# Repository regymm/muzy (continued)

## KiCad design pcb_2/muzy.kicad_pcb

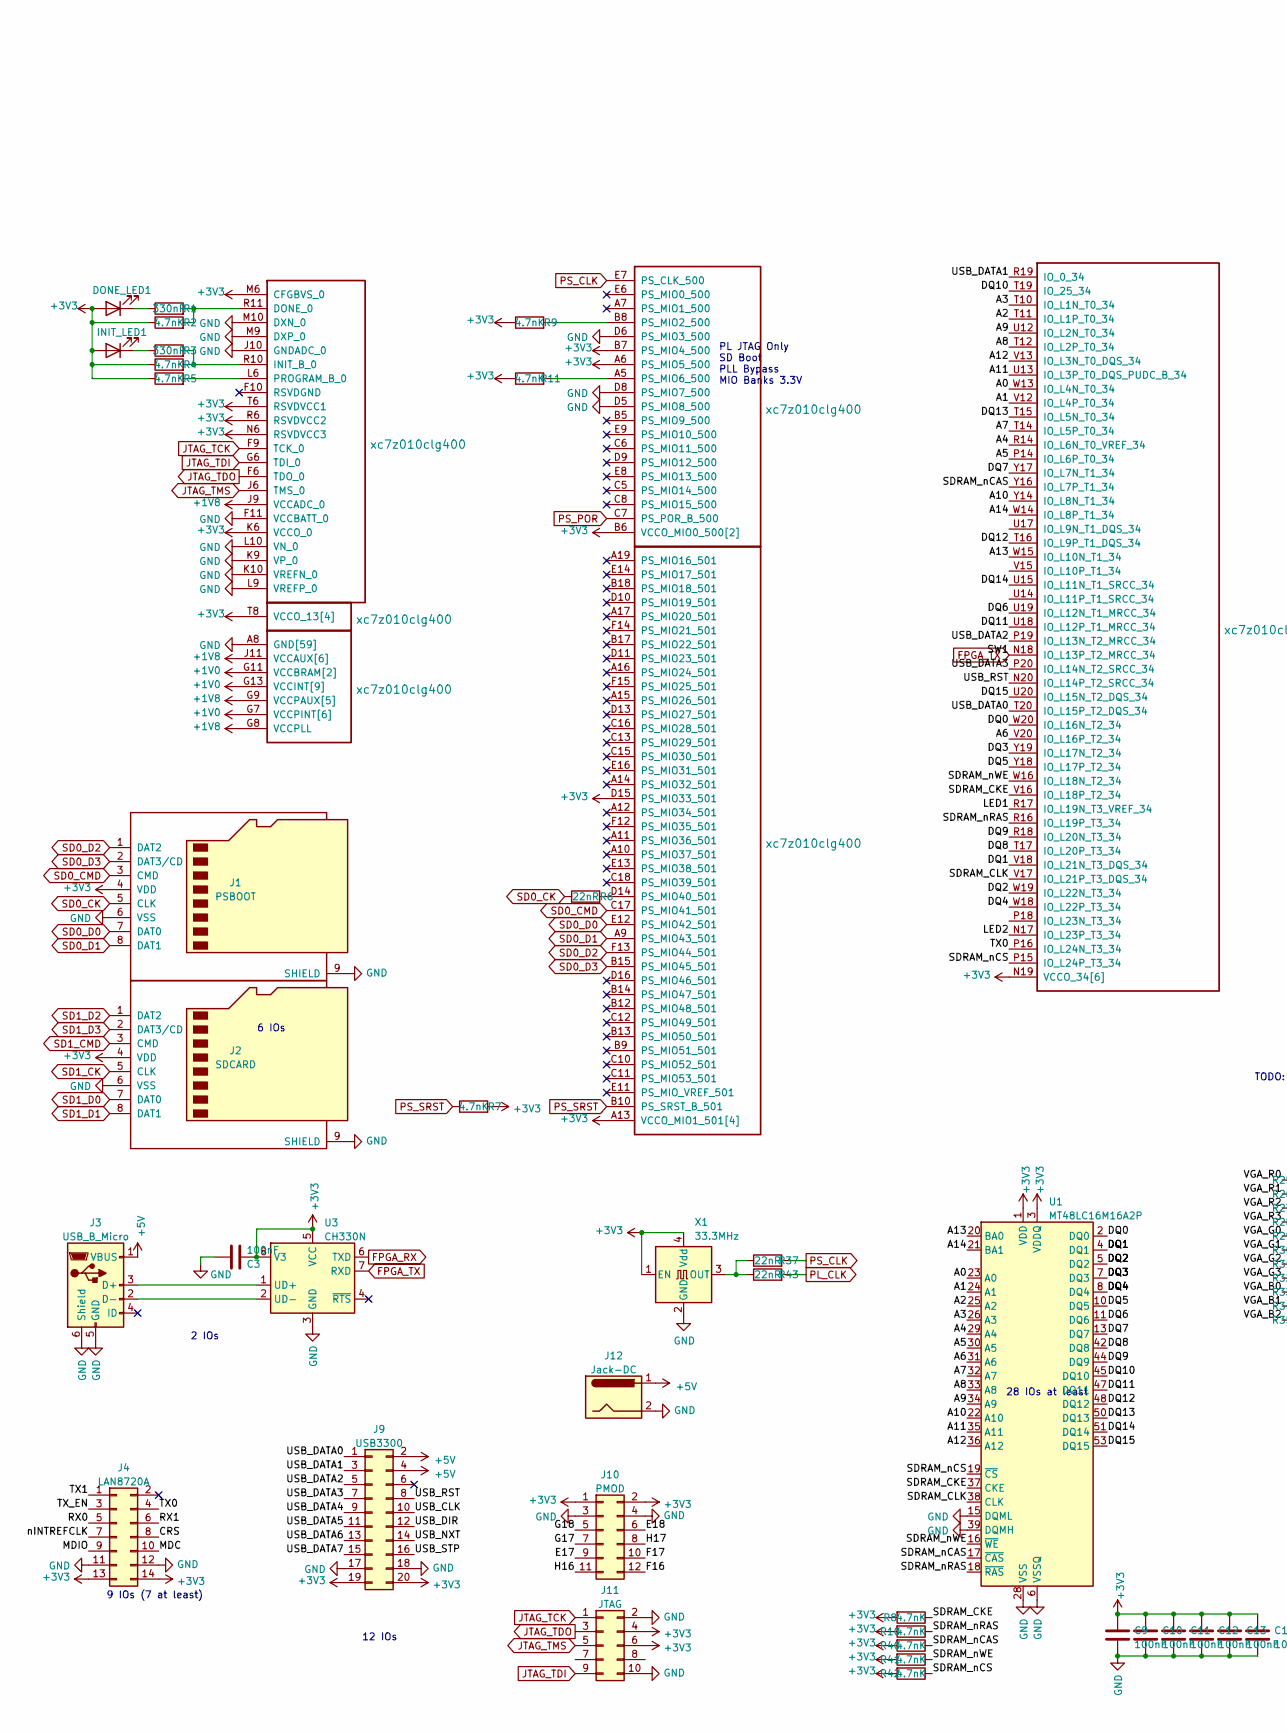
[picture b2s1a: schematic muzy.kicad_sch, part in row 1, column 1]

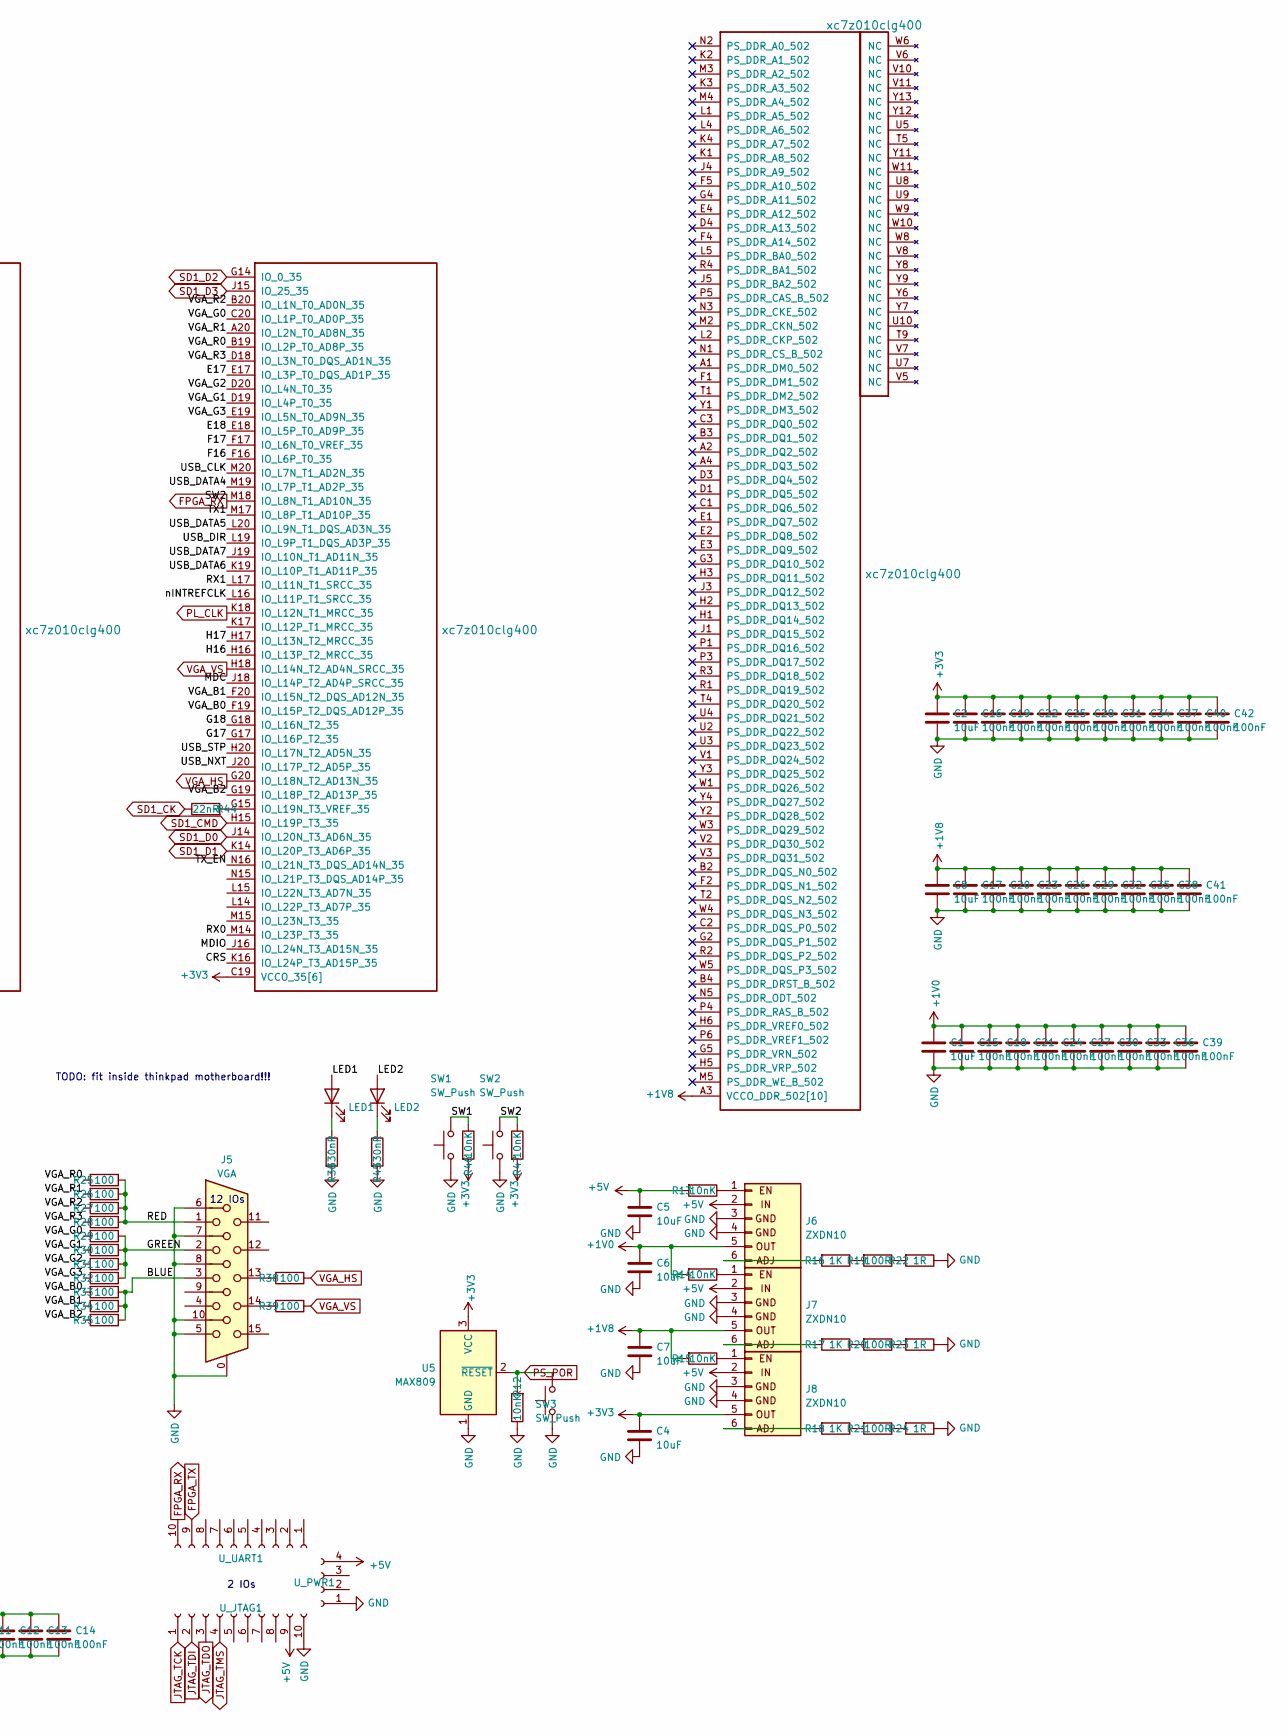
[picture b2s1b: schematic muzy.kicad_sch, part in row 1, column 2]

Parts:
C1, C2, C8: 10uF; C_0402_1005Metric
C3, C9, C10, C11, C12, C13, C14: 100nF; C_0603_1608Metric_Pad1.08x0.95mm_HandSolder
C4, C5, C6, C7: 10uF; C_0603_1608Metric_Pad1.08x0.95mm_HandSolder
C15, C16, C17, C18, C19, C20, C21, C22, C23, C24, C25, C26, C27, C28, C29, C30, C31, C32, C33, C34, C35, C36, C37, C38, C39, C40, C41, C42: 100nF; C_0402_1005Metric
DONE_LED1: LED; LED_0603_1608Metric_Pad1.05x0.95mm_HandSolder
INIT_LED1: LED; LED_0603_1608Metric_Pad1.05x0.95mm_HandSolder
J1: PSBOOT; SDMICRO_AT
J2: SDCARD; SDMICRO_AT
J3: USB_B_Micro; USB_Micro-B_Amphenol_10103594-0001LF_Horizontal
J4: LAN8720A; PinSocket_2x07_P2.54mm_Horizontal
J5: VGA; DSUB-15-HD_Female_Horizontal_P2.29x1.98mm_EdgePinOffset3.03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
J6, J7, J8: ZXDN10; ZX
J9: USB3300; PinSocket_2x10_P2.54mm_Horizontal
J10: PMOD; PinSocket_2x06_P2.54mm_Horizontal
J11: JTAG; PinHeader_2x05_P2.54mm_Vertical
J12: Jack-DC; BarrelJack_Wuerth_6941xx301002
LED1, LED2: LED; LED_0603_1608Metric_Pad1.05x0.95mm_HandSolder
R1, R3, R36, R45: 330nR; R_0603_1608Metric_Pad0.98x0.95mm_HandSolder
R2, R4, R5, R7, R8, R9, R10, R11, R40, R41, R42: 4.7nK; R_0603_1608Metric_Pad0.98x0.95mm_HandSolder
R6, R37, R43, R44: 22nR; R_0603_1608Metric_Pad0.98x0.95mm_HandSolder
R12, R13, R14, R15, R46, R47: 10nK; R_0603_1608Metric_Pad0.98x0.95mm_HandSolder
R16, R17, R18: 1K; R_0603_1608Metric_Pad0.98x0.95mm_HandSolder
R19, R20, R21: 100R; R_0603_1608Metric_Pad0.98x0.95mm_HandSolder
R22, R23, R24: 1R; R_0603_1608Metric_Pad0.98x0.95mm_HandSolder
R25, R26, R27, R28, R29, R30, R31, R32, R33, R34, R35, R38, R39: 100; R_0603_1608Metric_Pad0.98x0.95mm_HandSolder
SW1, SW2, SW3: SW_Push; SW_Push_SPST_NO_Alps_SKRK
U1: MT48LC16M16A2P; TSOP-II-54_22.2x10.16mm_P0.8mm
U2: xc7z010clg400; Xilinx_CLG400_smallpad
U3: CH330N; SOIC-8_3.9x4.9mm_P1.27mm
U5: MAX809; SOT-23
U_JTAG1: Conn_01x10_Female; PinSocket_1x10_P2.54mm_Vertical
U_PWR1: Conn_01x04_Female; PinSocket_1x04_P2.54mm_Vertical
U_UART1: Conn_01x10_Female; PinSocket_1x10_P2.54mm_Vertical
X1: 33.3MHz; Crystal_SMD_3225-4Pin_3.2x2.5mm

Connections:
+1V0: C1.1, C6.1, C15.1, C18.1, C21.1, C24.1, C27.1, C30.1, C33.1, C36.1, C39.1, J6.5 (OUT), R14.2, U2.G7 (VCCPINT[6]), U2.G11 (VCCBRAM[2]), U2.G13 (VCCINT[9]), U2.H10 (VCCBRAM[2]), U2.H12 (VCCINT[9]), U2.J7 (VCCPINT[6]), U2.J13 (VCCINT[9]), U2.K12 (VCCINT[9]), U2.L7 (VCCPINT[6]), U2.L13 (VCCINT[9]), U2.M12 (VCCINT[9]), U2.N7 (VCCPINT[6]), U2.N13 (VCCINT[9]), U2.P8 (VCCPINT[6]), U2.P12 (VCCINT[9]), U2.R7 (VCCPINT[6]), U2.R13 (VCCINT[9])
+1V8: C7.1, C8.1, C17.1, C20.1, C23.1, C26.1, C29.1, C32.1, C35.1, C38.1, C41.1, J7.5 (OUT), R15.2, U2.A3 (VCCO_DDR_502[10]), U2.D2 (VCCO_DDR_502[10]), U2.E5 (VCCO_DDR_502[10]), U2.F8 (VCCPAUX[5]), U2.G1 (VCCO_DDR_502[10]), U2.G8 (VCCPLL), U2.G9 (VCCPAUX[5]), U2.H4 (VCCO_DDR_502[10]), U2.H8 (VCCPAUX[5]), U2.J9 (VCCADC_0), U2.J11 (VCCAUX[6]), U2.K8 (VCCPAUX[5]), U2.L3 (VCCO_DDR_502[10]), U2.L11 (VCCAUX[6]), U2.M8 (VCCPAUX[5]), U2.N9 (VCCAUX[6]), U2.N11 (VCCAUX[6]), U2.P2 (VCCO_DDR_502[10]), U2.P10 (VCCAUX[6]), U2.R5 (VCCO_DDR_502[10]), U2.R9 (VCCAUX[6]), U2.U1 (VCCO_DDR_502[10]), U2.V4 (VCCO_DDR_502[10])
+3V3: C2.1, C3.1, C4.1, C9.1, C10.1, C11.1, C12.1, C13.1, C14.1, C16.1, C19.1, C22.1, C25.1, C28.1, C31.1, C34.1, C37.1, C40.1, C42.1, DONE_LED1.2 (A), INIT_LED1.2 (A), J1.4 (VDD), J2.4 (VDD), J4.13, J4.14, J8.5 (OUT), J9.19, J9.20, J10.1, J10.2, J11.4, J11.6, R2.1, R4.1, R5.1, R7.2, R8.2, R9.1, R10.2, R11.1, R40.2, R41.2, R42.2, R46.2, R47.2, U1.1 (VDD), U1.3 (VDDQ), U1.9 (VDDQ), U1.14 (VDD), U1.27 (VDD), U1.43 (VDDQ), U1.49 (VDDQ), U2.A6 (PS_MIO5_500), U2.A13 (VCCO_MIO1_501[4]), U2.B6 (VCCO_MIO0_500[2]), U2.B7 (PS_MIO4_500), U2.B16 (VCCO_MIO1_501[4]), U2.C19 (VCCO_35[6]), U2.D7 (VCCO_MIO0_500[2]), U2.D12 (VCCO_MIO1_501[4]), U2.D15 (PS_MIO33_501), U2.E15 (VCCO_MIO1_501[4]), U2.F18 (VCCO_35[6]), U2.H14 (VCCO_35[6]), U2.J17 (VCCO_35[6]), U2.K6 (VCCO_0), U2.K20 (VCCO_35[6]), U2.M6 (CFGBVS_0), U2.M16 (VCCO_35[6]), U2.N6 (RSVDVCC3), U2.N19 (VCCO_34[6]), U2.R6 (RSVDVCC2), U2.R15 (VCCO_34[6]), U2.T6 (RSVDVCC1), U2.T8 (VCCO_13[4]), U2.T18 (VCCO_34[6]), U2.U11 (VCCO_13[4]), U2.V14 (VCCO_34[6]), U2.W7 (VCCO_13[4]), U2.W17 (VCCO_34[6]), U2.Y10 (VCCO_13[4]), U2.Y20 (VCCO_34[6]), U3.5 (VCC), U3.8 (V3), U5.3 (VCC), X1.1 (EN), X1.4 (Vdd)
+5V: C5.1, J3.1 (VBUS), J6.2 (IN), J7.2 (IN), J8.2 (IN), J9.2, J9.4, J12.1, R13.2, U_JTAG1.9, U_PWR1.4
/A0: U1.23 (A0), U2.W13 (IO_L4N_T0_34)
/A1: U1.24 (A1), U2.V12 (IO_L4P_T0_34)
/A2: U1.25 (A2), U2.T11 (IO_L1P_T0_34)
/A3: U1.26 (A3), U2.T10 (IO_L1N_T0_34)
/A4: U1.29 (A4), U2.R14 (IO_L6N_T0_VREF_34)
/A5: U1.30 (A5), U2.P14 (IO_L6P_T0_34)
/A6: U1.31 (A6), U2.V20 (IO_L16P_T2_34)
/A7: U1.32 (A7), U2.T14 (IO_L5P_T0_34)
/A8: U1.33 (A8), U2.T12 (IO_L2P_T0_34)
/A9: U1.34 (A9), U2.U12 (IO_L2N_T0_34)
/A10: U1.22 (A10), U2.Y14 (IO_L8N_T1_34)
/A11: U1.35 (A11), U2.U13 (IO_L3P_T0_DQS_PUDC_B_34)
/A12: U1.36 (A12), U2.V13 (IO_L3N_T0_DQS_34)
/A13: U1.20 (BA0), U2.W15 (IO_L10N_T1_34)
/A14: U1.21 (BA1), U2.W14 (IO_L8P_T1_34)
/BLUE: J5.3, R33.1, R34.1, R35.1
/CRS: J4.8, U2.K16 (IO_L24P_T3_AD15P_35)
/DQ0: U1.2 (DQ0), U2.W20 (IO_L16N_T2_34)
/DQ1: U1.4 (DQ1), U2.V18 (IO_L21N_T3_DQS_34)
/DQ2: U1.5 (DQ2), U2.W19 (IO_L22N_T3_34)
/DQ3: U1.7 (DQ3), U2.Y19 (IO_L17N_T2_34)
/DQ4: U1.8 (DQ4), U2.W18 (IO_L22P_T3_34)
/DQ5: U1.10 (DQ5), U2.Y18 (IO_L17P_T2_34)
/DQ6: U1.11 (DQ6), U2.U19 (IO_L12N_T1_MRCC_34)
/DQ7: U1.13 (DQ7), U2.Y17 (IO_L7N_T1_34)
/DQ8: U1.42 (DQ8), U2.T17 (IO_L20P_T3_34)
/DQ9: U1.44 (DQ9), U2.R18 (IO_L20N_T3_34)
/DQ10: U1.45 (DQ10), U2.T19 (IO_25_34)
/DQ11: U1.47 (DQ11), U2.U18 (IO_L12P_T1_MRCC_34)
/DQ12: U1.48 (DQ12), U2.T16 (IO_L9P_T1_DQS_34)
/DQ13: U1.50 (DQ13), U2.T15 (IO_L5N_T0_34)
/DQ14: U1.51 (DQ14), U2.U15 (IO_L11N_T1_SRCC_34)
/DQ15: U1.53 (DQ15), U2.U20 (IO_L15N_T2_DQS_34)
/E17: J10.9, U2.E17 (IO_L3P_T0_DQS_AD1P_35)
/E18: J10.6, U2.E18 (IO_L5P_T0_AD9P_35)
/F16: J10.12, U2.F16 (IO_L6P_T0_35)
/F17: J10.10, U2.F17 (IO_L6N_T0_VREF_35)
/G17: J10.7, U2.G17 (IO_L16P_T2_35)
/G18: J10.5, U2.G18 (IO_L16N_T2_35)
/GREEN: J5.2, R29.1, R30.1, R31.1, R32.1
/H16: J10.11, U2.H16 (IO_L13P_T2_MRCC_35)
/H17: J10.8, U2.H17 (IO_L13N_T2_MRCC_35)
/LED1: LED1.2 (A), U2.R17 (IO_L19N_T3_VREF_34)
/LED2: LED2.2 (A), U2.N17 (IO_L23P_T3_34)
/MDC: J4.10, U2.J18 (IO_L14P_T2_AD4P_SRCC_35)
/MDIO: J4.9, U2.J16 (IO_L24N_T3_AD15N_35)
/RED: J5.1, R25.1, R26.1, R27.1, R28.1
/RX0: J4.5, U2.M14 (IO_L23P_T3_35)
/RX1: J4.6, U2.L17 (IO_L11N_T1_SRCC_35)
/SDRAM_CKE: R8.1, U1.37 (CKE), U2.V16 (IO_L18P_T2_34)
/SDRAM_CLK: U1.38 (CLK), U2.V17 (IO_L21P_T3_DQS_34)
/SDRAM_nCAS: R40.1, U1.17 (~CAS), U2.Y16 (IO_L7P_T1_34)
/SDRAM_nCS: R42.1, U1.19 (~CS), U2.P15 (IO_L24P_T3_34)
/SDRAM_nRAS: R10.1, U1.18 (~RAS), U2.R16 (IO_L19P_T3_34)
/SDRAM_nWE: R41.1, U1.16 (~WE), U2.W16 (IO_L18N_T2_34)
/TX0: J4.4, U2.P16 (IO_L24N_T3_34)
/TX1: J4.1, U2.M17 (IO_L8P_T1_AD10P_35)
/TX_EN: J4.3, U2.N16 (IO_L21N_T3_DQS_AD14N_35)
/USB_CLK: J9.10, U2.M20 (IO_L7N_T1_AD2N_35)
/USB_DATA0: J9.1, U2.T20 (IO_L15P_T2_DQS_34)
/USB_DATA1: J9.3, U2.R19 (IO_0_34)
/USB_DATA2: J9.5, U2.P19 (IO_L13N_T2_MRCC_34)
/USB_DATA3: J9.7, U2.P20 (IO_L14N_T2_SRCC_34)
/USB_DATA4: J9.9, U2.M19 (IO_L7P_T1_AD2P_35)
/USB_DATA5: J9.11, U2.L20 (IO_L9N_T1_DQS_AD3N_35)
/USB_DATA6: J9.13, U2.K19 (IO_L10P_T1_AD11P_35)
/USB_DATA7: J9.15, U2.J19 (IO_L10N_T1_AD11N_35)
/USB_DIR: J9.12, U2.L19 (IO_L9P_T1_DQS_AD3P_35)
/USB_NXT: J9.14, U2.J20 (IO_L17P_T2_AD5P_35)
/USB_RST: J9.8, U2.N20 (IO_L14P_T2_SRCC_34)
/USB_STP: J9.16, U2.H20 (IO_L17N_T2_AD5N_35)
/VGA_B0: R33.2, U2.F19 (IO_L15P_T2_DQS_AD12P_35)
/VGA_B1: R34.2, U2.F20 (IO_L15N_T2_DQS_AD12N_35)
/VGA_B2: R35.2, U2.G19 (IO_L18P_T2_AD13P_35)
/VGA_G0: R29.2, U2.C20 (IO_L1P_T0_AD0P_35)
/VGA_G1: R30.2, U2.D19 (IO_L4P_T0_35)
/VGA_G2: R31.2, U2.D20 (IO_L4N_T0_35)
/VGA_G3: R32.2, U2.E19 (IO_L5N_T0_AD9N_35)
/VGA_R0: R25.2, U2.B19 (IO_L2P_T0_AD8P_35)
/VGA_R1: R26.2, U2.A20 (IO_L2N_T0_AD8N_35)
/VGA_R2: R27.2, U2.B20 (IO_L1N_T0_AD0N_35)
/VGA_R3: R28.2, U2.D18 (IO_L3N_T0_DQS_AD1N_35)
/nINTREFCLK: J4.7, U2.L16 (IO_L11P_T1_SRCC_35)
FPGA_RX: R47.1, SW2.2, U2.M18 (IO_L8N_T1_AD10N_35), U3.6 (TXD), U_UART1.10
FPGA_TX: R46.1, SW1.2, U2.N18 (IO_L13P_T2_MRCC_34), U3.7 (RXD), U_UART1.9
GND: C1.2, C2.2, C3.2, C4.2, C5.2, C6.2, C7.2, C8.2, C9.2, C10.2, C11.2, C12.2, C13.2, C14.2, C15.2, C16.2, C17.2, C18.2, C19.2, C20.2, C21.2, C22.2, C23.2, C24.2, C25.2, C26.2, C27.2, C28.2, C29.2, C30.2, C31.2, C32.2, C33.2, C34.2, C35.2, C36.2, C37.2, C38.2, C39.2, C40.2, C41.2, C42.2, J1.6 (VSS), J1.9 (SHIELD), J2.6 (VSS), J2.9 (SHIELD), J3.5 (GND), J3.6 (Shield), J4.11, J4.12, J5.0, J5.5, J5.6, J5.7, J5.8, J5.10, J6.3 (GND), J6.4 (GND), J7.3 (GND), J7.4 (GND), J8.3 (GND), J8.4 (GND), J9.17, J9.18, J10.3, J10.4, J11.2, J11.10, J12.2, R12.1, R22.1, R23.1, R24.1, R36.2, R45.2, SW1.1, SW2.1, SW3.1, U1.6 (VSSQ), U1.12 (VSSQ), U1.15 (DQML), U1.28 (VSS), U1.39 (DQMH), U1.41 (VSS), U1.46 (VSSQ), U1.52 (VSSQ), U1.54 (VSS), U2.A8 (GND[59]), U2.A18 (GND[59]), U2.B1 (GND[59]), U2.B11 (GND[59]), U2.C4 (GND[59]), U2.C9 (GND[59]), U2.C14 (GND[59]), U2.D5 (PS_MIO8_500), U2.D6 (PS_MIO3_500), U2.D8 (PS_MIO7_500), U2.D17 (GND[59]), U2.E10 (GND[59]), U2.E20 (GND[59]), U2.F3 (GND[59]), U2.F7 (GND[59]), U2.F11 (VCCBATT_0), U2.G10 (GND[59]), U2.G12 (GND[59]), U2.G16 (GND[59]), U2.H7 (GND[59]), U2.H9 (GND[59]), U2.H11 (GND[59]), U2.H13 (GND[59]), U2.H19 (GND[59]), U2.J2 (GND[59]), U2.J8 (GND[59]), U2.J10 (GNDADC_0), U2.J12 (GND[59]), U2.K5 (GND[59]), U2.K7 (GND[59]), U2.K9 (VP_0), U2.K10 (VREFN_0), U2.K11 (GND[59]), U2.K13 (GND[59]), U2.K15 (GND[59]), U2.L8 (GND[59]), U2.L9 (VREFP_0), U2.L10 (VN_0), U2.L12 (GND[59]), U2.L18 (GND[59]), U2.M1 (GND[59]), U2.M7 (GND[59]), U2.M9 (DXP_0), U2.M10 (DXN_0), U2.M11 (GND[59]), U2.M13 (GND[59]), U2.N4 (GND[59]), U2.N8 (GND[59]), U2.N10 (GND[59]), U2.N12 (GND[59]), U2.N14 (GND[59]), U2.P7 (GND[59]), U2.P9 (GND[59]), U2.P11 (GND[59]), U2.P13 (GND[59]), U2.P17 (GND[59]), U2.R8 (GND[59]), U2.R12 (GND[59]), U2.R20 (GND[59]), U2.T3 (GND[59]), U2.T7 (GND[59]), U2.T13 (GND[59]), U2.U6 (GND[59]), U2.U16 (GND[59]), U2.V9 (GND[59]), U2.V19 (GND[59]), U2.W2 (GND[59]), U2.W12 (GND[59]), U2.Y5 (GND[59]), U2.Y15 (GND[59]), U3.3 (GND), U5.1 (GND), U_JTAG1.10, U_PWR1.1, X1.2 (GND)
JTAG_TCK: J11.1, U2.F9 (TCK_0), U_JTAG1.1
JTAG_TDI: J11.9, U2.G6 (TDI_0), U_JTAG1.2
JTAG_TDO: J11.3, U2.F6 (TDO_0), U_JTAG1.3
JTAG_TMS: J11.5, U2.J6 (TMS_0), U_JTAG1.4
unnamed: DONE_LED1.1 (K), R1.1
unnamed: INIT_LED1.1 (K), R3.1
unnamed: J3.2 (D-), U3.2 (UD-)
unnamed: J3.3 (D+), U3.1 (UD+)
unnamed: J5.13, R38.2
unnamed: J5.14, R39.2
unnamed: J6.1 (EN), R13.1
unnamed: J6.6 (ADJ), R16.2
unnamed: J7.1 (EN), R14.1
unnamed: J7.6 (ADJ), R17.2
unnamed: J8.1 (EN), R15.1
unnamed: J8.6 (ADJ), R18.2
unnamed: LED1.1 (K), R36.1
unnamed: LED2.1 (K), R45.1
unnamed: R1.2, R2.2, U2.R11 (DONE_0)
unnamed: R3.2, R4.2, U2.R10 (INIT_B_0)
unnamed: R5.2, U2.L6 (PROGRAM_B_0)
unnamed: R6.2, U2.D14 (PS_MIO40_501)
unnamed: R9.2, U2.B8 (PS_MIO2_500)
unnamed: R11.2, U2.A5 (PS_MIO6_500)
unnamed: R16.1, R19.2
unnamed: R17.1, R20.2
unnamed: R18.1, R21.2
unnamed: R19.1, R22.2
unnamed: R20.1, R23.2
unnamed: R21.1, R24.2
unnamed: R37.1, R43.1, X1.3 (OUT)
unnamed: R44.2, U2.G15 (IO_L19N_T3_VREF_35)
PL_CLK: R43.2, U2.K18 (IO_L12N_T1_MRCC_35)
PS_CLK: R37.2, U2.E7 (PS_CLK_500)
PS_POR: R12.2, SW3.2, U2.C7 (PS_POR_B_500), U5.2 (~RESET)
PS_SRST: R7.1, U2.B10 (PS_SRST_B_501)
SD0_CK: J1.5 (CLK), R6.1
SD0_CMD: J1.3 (CMD), U2.C17 (PS_MIO41_501)
SD0_D0: J1.7 (DAT0), U2.E12 (PS_MIO42_501)
SD0_D1: J1.8 (DAT1), U2.A9 (PS_MIO43_501)
SD0_D2: J1.1 (DAT2), U2.F13 (PS_MIO44_501)
SD0_D3: J1.2 (DAT3/CD), U2.B15 (PS_MIO45_501)
SD1_CK: J2.5 (CLK), R44.1
SD1_CMD: J2.3 (CMD), U2.H15 (IO_L19P_T3_35)
SD1_D0: J2.7 (DAT0), U2.J14 (IO_L20N_T3_AD6N_35)
SD1_D1: J2.8 (DAT1), U2.K14 (IO_L20P_T3_AD6P_35)
SD1_D2: J2.1 (DAT2), U2.G14 (IO_0_35)
SD1_D3: J2.2 (DAT3/CD), U2.J15 (IO_25_35)
VGA_HS: R38.1, U2.G20 (IO_L18N_T2_AD13N_35)
VGA_VS: R39.1, U2.H18 (IO_L14N_T2_AD4N_SRCC_35)

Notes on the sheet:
12 IOs
6 IOs
28 IOs at least
2 IOs
9 IOs (7 at least)
PL JTAG Only SD Boot PLL Bypass MIO Banks 3.3V
TODO: fit inside thinkpad motherboard!!!

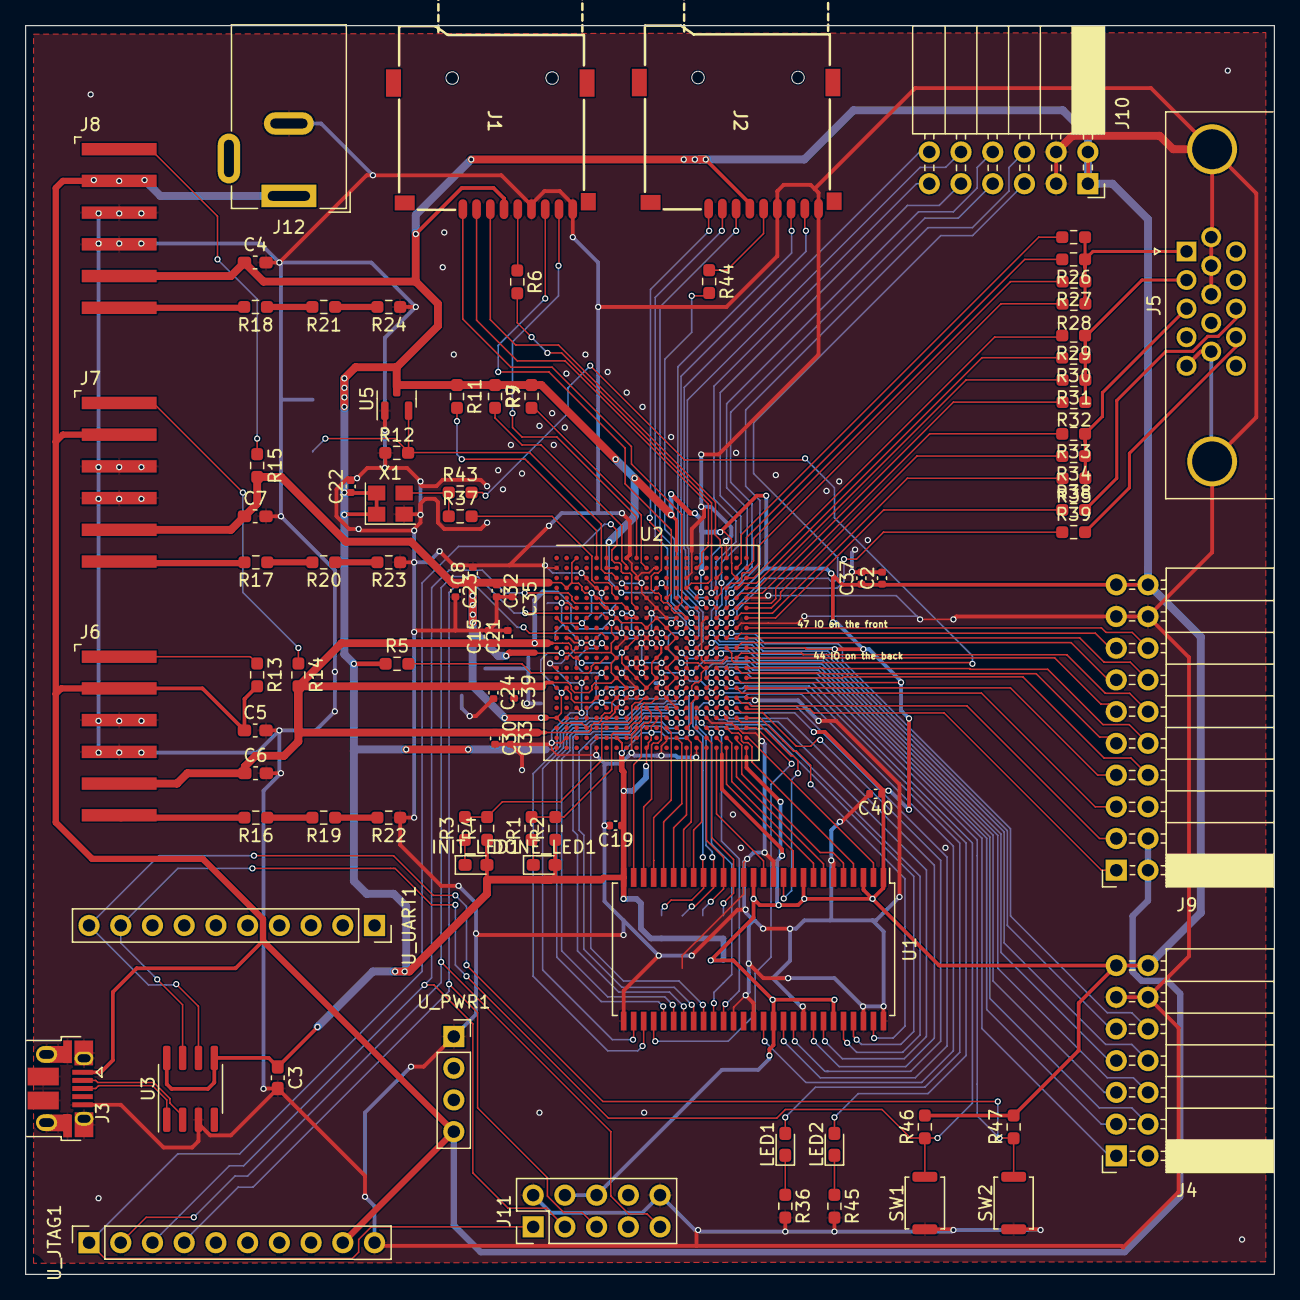
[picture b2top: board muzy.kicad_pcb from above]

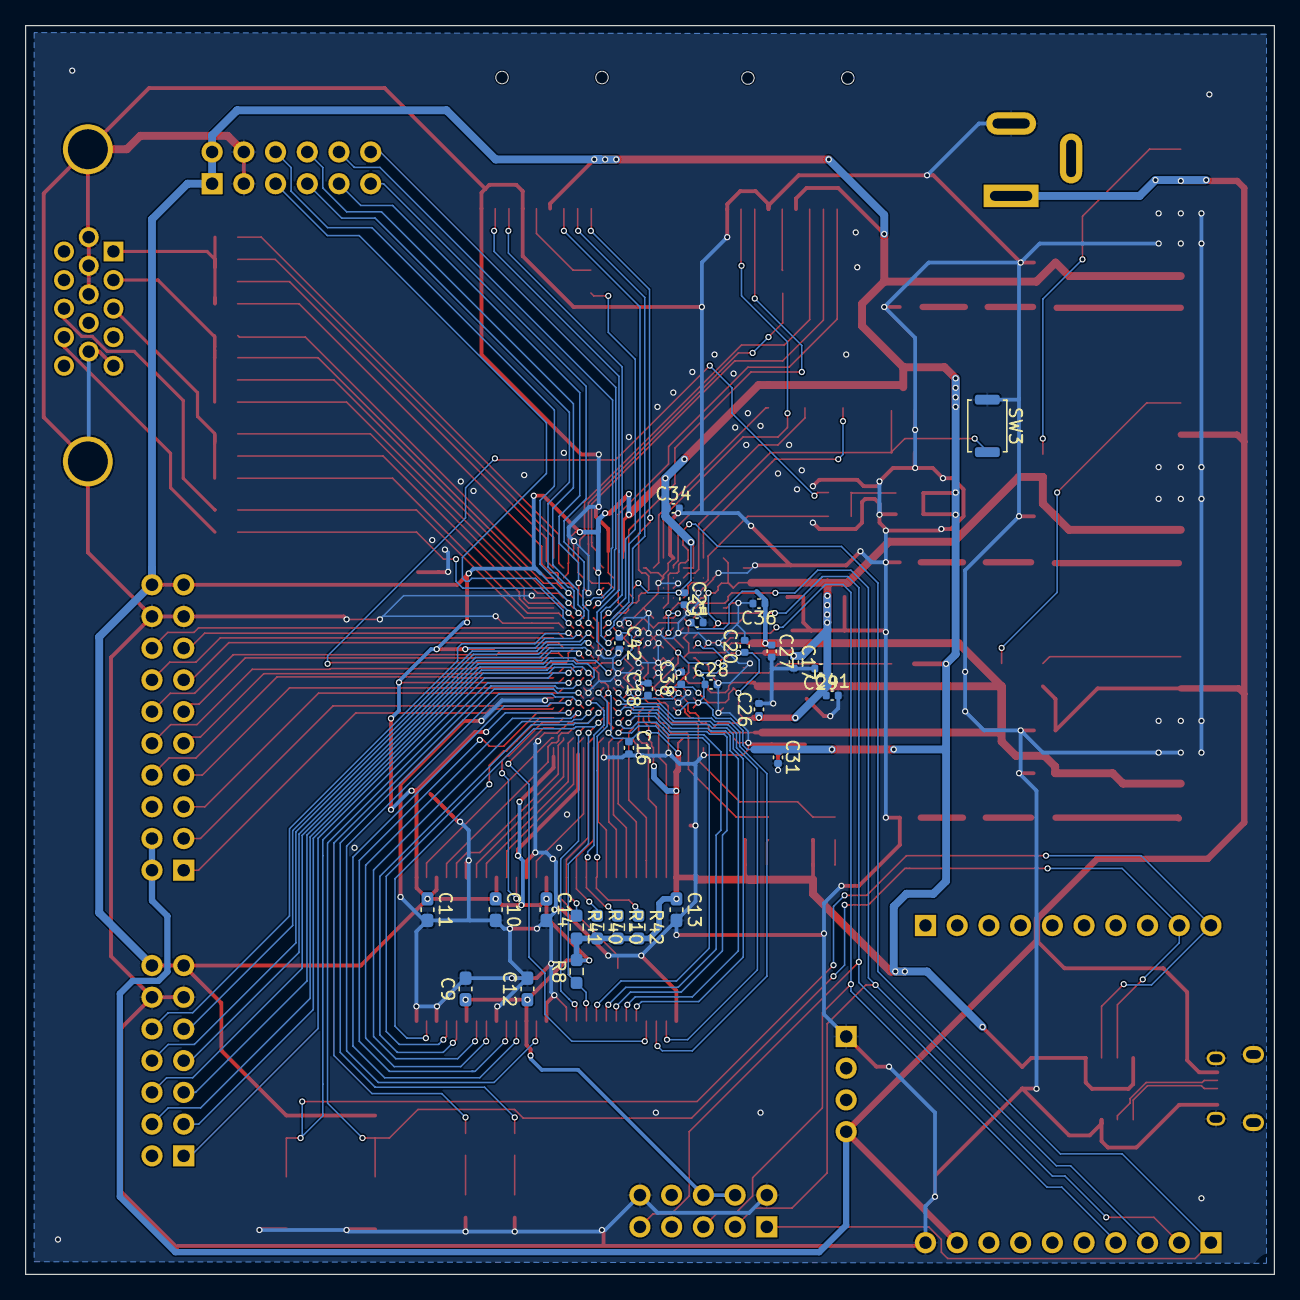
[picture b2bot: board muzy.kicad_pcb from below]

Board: 2 copper layers, 100.0 x 100.0 mm, 116 parts (28 on the bottom side), 140 nets.

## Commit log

2024-05-01 Added files and README
2024-06-13 Testing is now finished, update README and pictures
2024-09-29 added muzy 4
2026-01-06 Release muzy4
2026-03-30 Updated pico firmware usage
